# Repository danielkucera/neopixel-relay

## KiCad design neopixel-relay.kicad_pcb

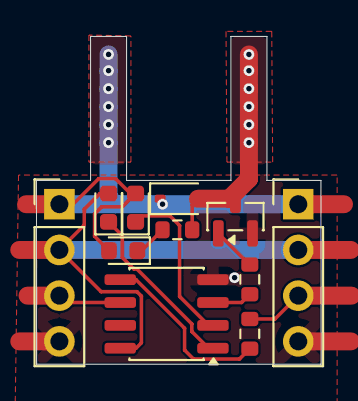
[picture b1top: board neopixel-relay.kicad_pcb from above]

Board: 2 copper layers, 15.8 x 18.2 mm, 11 parts (0 on the bottom side), 12 nets.

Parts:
D1, D2, D3: LED; LED_0603_1608Metric
D4: 1N5819WS; D_SOD-323
J1, J2: Conn_01x04_Pin; PinHeader_1x04_P2.54mm_Vertical
Q1: AO3400A; SOT-23
R1, R2, R3: R; R_0603_1608Metric
U1: WS2811; SO-8_3.9x4.9mm_P1.27mm

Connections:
GND: J1.4, J2.4, Q1.2 (S), U1.4 (GND)
unnamed: D1.2 (A), D3.2 (A), D4.1 (K), J1.1, J2.1
unnamed: D1.1 (K), R3.2
unnamed: D2.2 (A), J1.2, J2.2, U1.8 (VDD)
unnamed: D2.1 (K), U1.1 (OUTR)
unnamed: D3.1 (K), U1.2 (OUTG)
unnamed: D4.2 (A), Q1.3 (D), R3.1
unnamed: J1.3, U1.6 (DIN)
unnamed: J2.3, R2.2
unnamed: Q1.1 (G), R1.2
unnamed: R2.1, U1.5 (DO)
unnamed: R1.1, U1.3 (OUTB)
